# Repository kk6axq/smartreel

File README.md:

# SmartReel

SmartReel is a smart storage rack for reels of surface-mount electronic
components that works hand-in-hand with [InvenTree](https://inventree.org/),
an open-source inventory management system. The rack is built from one or more
**reel modules**, each a row of slots; every slot senses whether a reel is
present, has an addressable RGB LED to guide the operator, and can be widened by
pulling **dividers**. A touchscreen **HMI** mounted on the rack is the operator's
control panel — it talks to the rack hardware over RS485 and to InvenTree over
HTTPS. InvenTree stays the single source of truth for inventory; SmartReel
records *where* each reel physically lives and lights slots to guide pick and
put-away. The operator scans a reel, the rack lights up, and the inventory
updates itself.

## Project status & disclaimer

This project was developed with substantial AI assistance (using large language
models as a coding and documentation aid). The hardware, firmware, and plugin
have been built and run on real SmartReel hardware, and the core workflows have
been exercised on the bench and in use — but this is **not infallible software**.
It has not been through formal verification or a third-party audit, it almost
certainly contains bugs, and both the code and the docs may be incomplete or
occasionally wrong.

Treat it as a working reference design, not a turnkey product:

- Review the code yourself before relying on it, and read
  [`docs/known-bugs.md`](docs/known-bugs.md) for known limitations.
- **Security:** the HMI currently talks to InvenTree over HTTPS *without*
  certificate verification (`setInsecure()`), so the auth token is exposed to
  on-path attackers. Do not deploy on an untrusted network until certificate
  pinning is in place — see [`docs/known-bugs.md`](docs/known-bugs.md).
- It is provided as-is, with no warranty. You are responsible for validating it
  for your own use, especially anything safety- or inventory-critical.

Issues and pull requests that fix bugs or fill gaps are welcome.

## Repository layout

```
esp32-hmi/         ESP32-S3 touchscreen HMI firmware (C++ / PlatformIO / LVGL)
core-fw/           RP2040 core firmware that drives the reel modules (C++ / PlatformIO)
inventree-plugin/  InvenTree server-side plugin (Python)
pcbs/              KiCad hardware designs
  CorePCB/           Core PCB
  ReelPCB/           reel module PCB
debug-fw/          Bench/debug tooling (not shipped)
  mock-inventree/    FastAPI stand-in for the plugin, used during HMI development
  core-hwtest/       RP2040 hardware bring-up test
  esp32-rs485-pintest/ standalone ESP32 RS485 pin-toggle tool
  inject.py          bench event injector (drives the core test rig over USB)
  sd-assets/         mock QR codes for bench-testing the scan->resolve flow
docs/              Project documentation (start at docs/README.md)
labels/            Printable slot label PDFs (make_labels.py; PDFs git-ignored)
scripts/           Flashing, SD deployment, QR generation helpers
```

## Documentation

The full documentation set lives under [`docs/`](docs/README.md). Start with the
[documentation index](docs/README.md), then dive into the manual chapters:

- [Concept of Operations](docs/manual/01-concept-of-operations.md) — what SmartReel is and the end-to-end workflows.
- [Hardware Structure](docs/manual/02-hardware.md) — rack, Core PCB, reel modules, LEDs, sensors, wiring.
- [Software Structure](docs/manual/03-software-architecture.md) — components, subsystems, and system data flow.
- [API Reference](docs/manual/04-api-reference.md) — the HMI↔plugin HTTP API and the RS485 wire protocol.
- [InvenTree Integration](docs/manual/05-inventree-integration.md) — the plugin, install/config, and the sync model.
- [Operator User Manual](docs/manual/06-operator-manual.md) — task-oriented guide for shop-floor operators.

## Build & flash

**HMI firmware** (`esp32-hmi/`) and **Core firmware** (`core-fw/`) are
[PlatformIO](https://platformio.org/) projects. Build and flash:

```bash
# HMI (ESP32-S3) — requires manual boot mode (hold BOOT, tap RESET, release BOOT)
cd esp32-hmi && pio run
./scripts/flash-hmi.sh

# Core (RP2040) — UF2 dropped onto the BOOTSEL drive
cd core-fw && pio run
./scripts/flash-core.sh
```

The flash scripts locate the boards by USB VID, so the order they are plugged in
does not matter. See [`scripts/`](scripts/) for SD deployment (`deploy-sd.sh`)
and QR generation helpers.

**InvenTree plugin** (`inventree-plugin/`) is a Python plugin installed into an
InvenTree instance. See [`inventree-plugin/README.md`](inventree-plugin/README.md)
for installation, configuration, and the docker dev workflow.

**Mock server** — for HMI development without a live InvenTree, the FastAPI mock
at [`debug-fw/mock-inventree/`](debug-fw/mock-inventree/) serves the same HTTPS
contract as the plugin. See its [README](debug-fw/mock-inventree/README.md).

## Tests

Host-runnable tests (no hardware or InvenTree install needed) live under
[`tests/`](tests/README.md): the shared RS485 frame codec (`cd tests && make`)
and the plugin's pure service logic (`cd inventree-plugin && python3
test_services.py`). The full contract is exercised against a live InvenTree by
`inventree-plugin/test_live.py` and `test_multirack.py`.

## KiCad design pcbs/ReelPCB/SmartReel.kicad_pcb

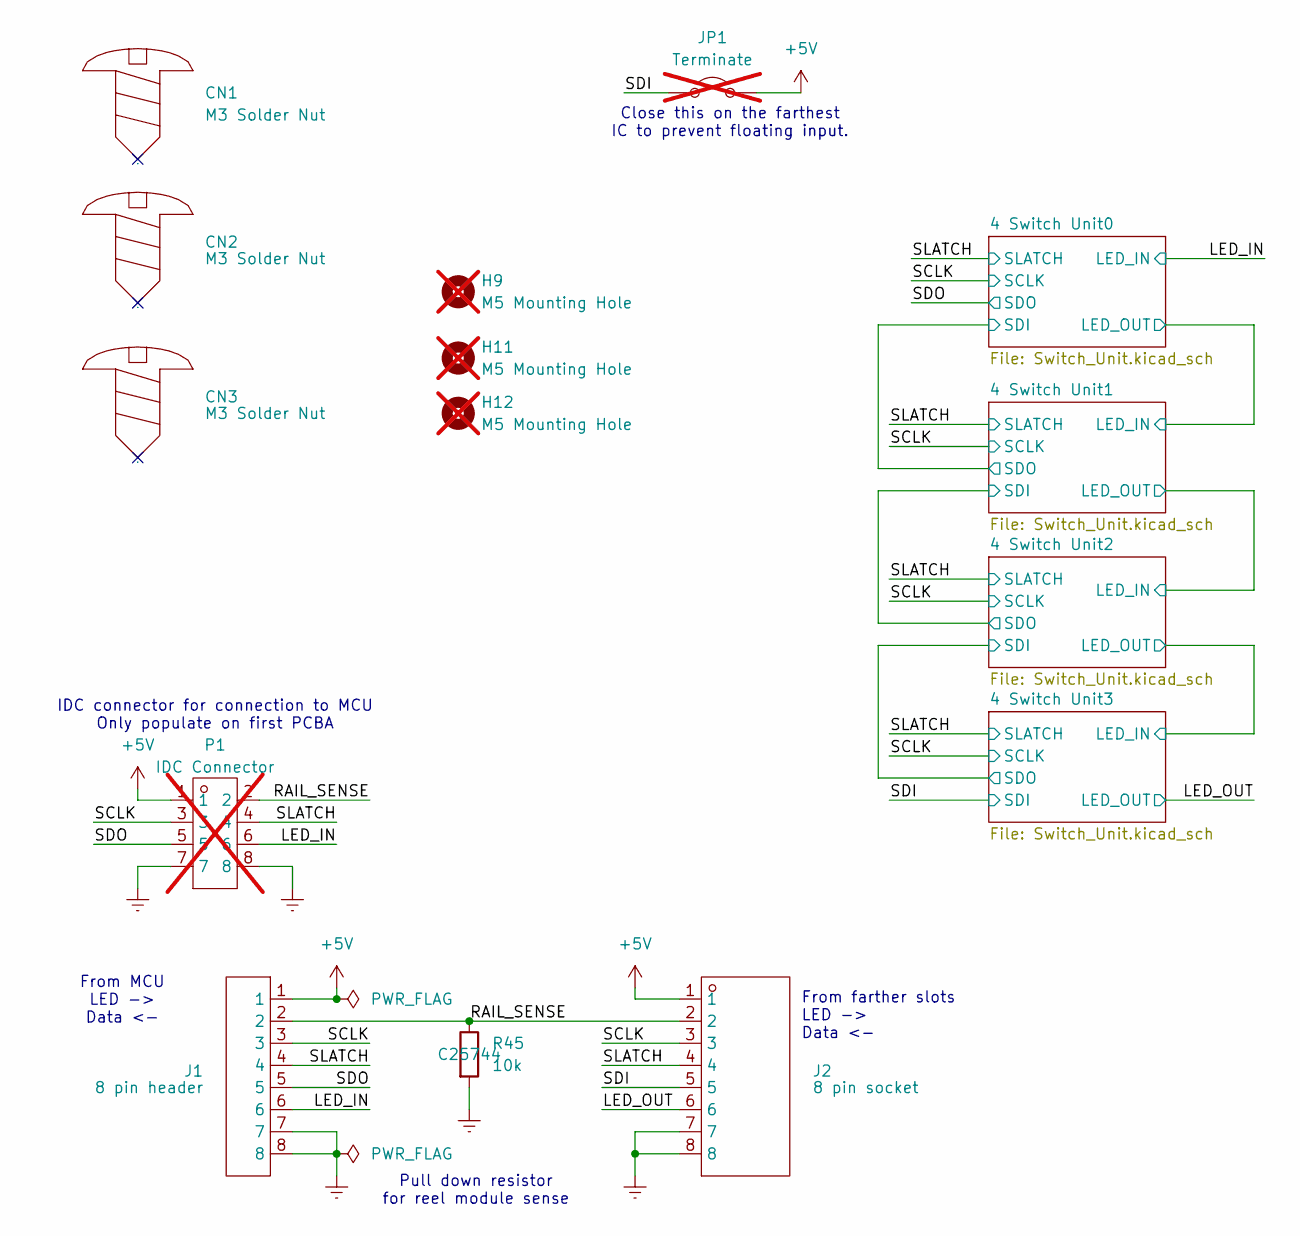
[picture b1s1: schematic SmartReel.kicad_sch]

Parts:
CN1, CN2, CN3: M3 Solder Nut; M3-TH_BD6.0-D4.3; Manufacturer Part SMTSOM330BTR; LCSC Part Name YIYUAN(怡远) 电路板表贴圆螺母柱 PCB贴片连接器 M3x5.56xL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
H9, H11, H12: M5 Mounting Hole; MountingHole_5.3mm_M5; not fitted
J1: 8 pin header; HDR-TH_8P-P2.54-H-M-W10.0; Manufacturer Part MTP125-1108R1; LCSC Part Name 1x8P 间距:2.54mm 方针 弯插
J2: 8 pin socket; HDR-TH_8P-P2.54-H-W8.6_A2541HWR-8P; Manufacturer Part A2541HWR-8P; LCSC Part Name 1x8P 间距:2.54mm 弯插
JP1: Terminate; SolderJumper-2_P1.3mm_Open_RoundedPad1.0x1.5mm; not fitted
P1: IDC Connector; IDC-TH_8P-P2.00_BOOMELE2X4P; Manufacturer Part 2.0-2*4P直简牛; LCSC Part Name 2mm 2x4P 排数:2 每排P数:4; not fitted
R45: 10k; R_0402_1005Metric

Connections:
+5V: J1.1, J2.1, JP1.2 (B), P1.1; also elsewhere on the board
/LED_IN: J1.6, P1.6; also elsewhere on the board
/LED_OUT: J2.6; also elsewhere on the board
/RAIL_SENSE: J1.2, J2.2, P1.2, R45.1
/SCLK: J1.3, J2.3, P1.3; also elsewhere on the board
/SDI: J2.5, JP1.1 (A); also elsewhere on the board
/SDO: J1.5, P1.5; also elsewhere on the board
/SLATCH: J1.4, J2.4, P1.4; also elsewhere on the board
Earth: J1.7, J1.8, J2.7, J2.8, P1.7, P1.8, R45.2; also elsewhere on the board

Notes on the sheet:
IDC connector for connection to MCU Only populate on first PCBA
Pull down resistor for reel module sense
Close this on the farthest IC to prevent floating input.
From MCU LED -> Data <-
From farther slots LED -> Data <-

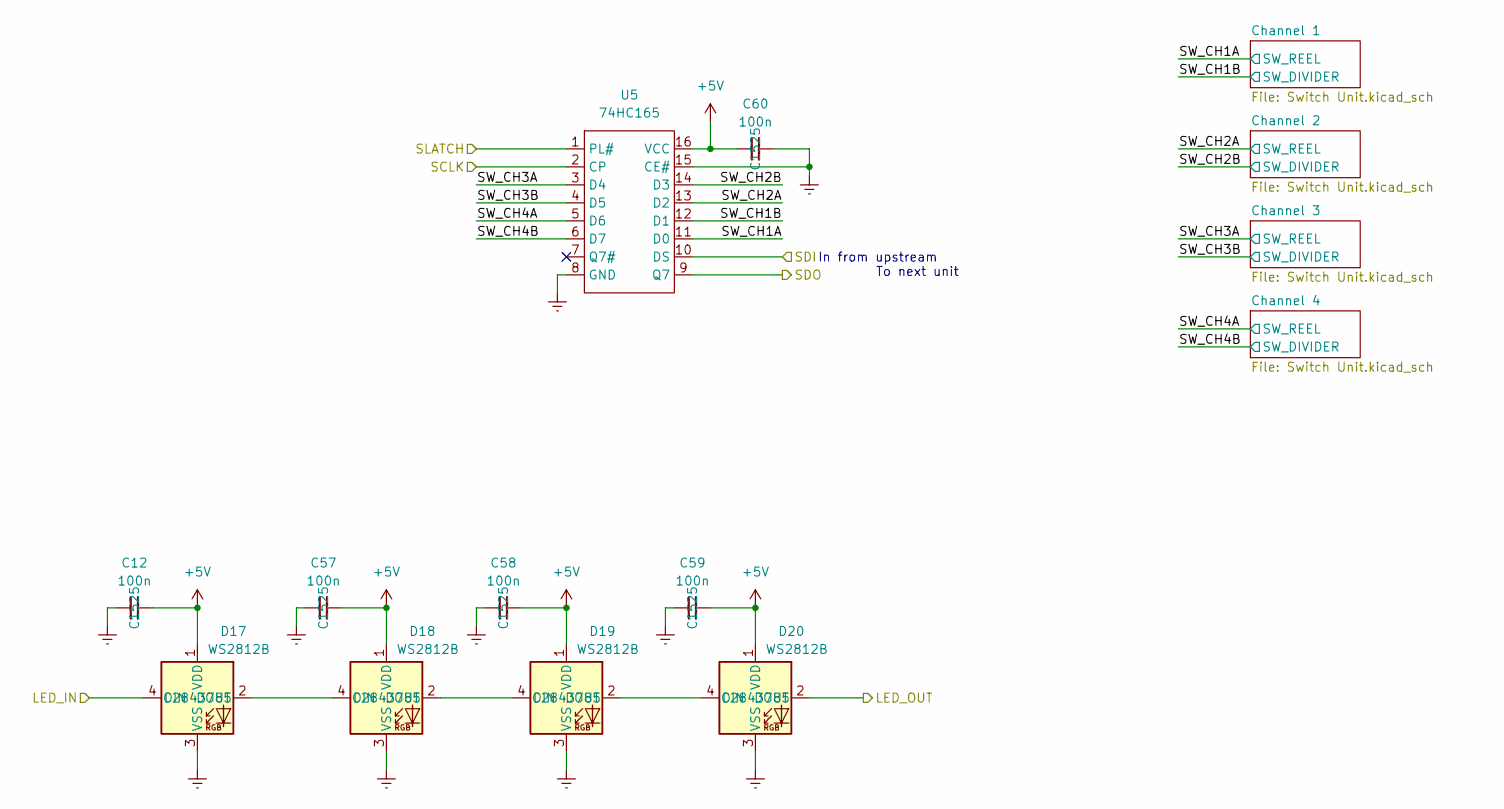
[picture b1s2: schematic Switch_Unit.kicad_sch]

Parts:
C12, C57, C58, C59, C60: 100n; C_0402_1005Metric
D17, D18, D19, D20: WS2812B; LED_WS2812B_PLCC4_5.0x5.0mm_P3.2mm
U5: 74HC165; SOIC-16_3.9x9.9mm_P1.27mm; Manufacturer Part 74HC165D,653; LCSC Part Name 补充型输出 并行或串行至串行移位寄存器

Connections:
+5V: C12.2, C57.2, C58.2, C59.2, C60.1, D17.1 (VDD), D18.1 (VDD), D19.1 (VDD), D20.1 (VDD), U5.16 (VCC); also elsewhere on the board
/4 Switch Unit0/LED_OUT: D20.2 (DOUT); also elsewhere on the board
/4 Switch Unit0/SDI: U5.10 (DS); also elsewhere on the board
/4 Switch Unit0/SW_CH1A: U5.11 (D0); also elsewhere on the board
/4 Switch Unit0/SW_CH1B: U5.12 (D1); also elsewhere on the board
/4 Switch Unit0/SW_CH2A: U5.13 (D2); also elsewhere on the board
/4 Switch Unit0/SW_CH2B: U5.14 (D3); also elsewhere on the board
/4 Switch Unit0/SW_CH3A: U5.3 (D4); also elsewhere on the board
/4 Switch Unit0/SW_CH3B: U5.4 (D5); also elsewhere on the board
/4 Switch Unit0/SW_CH4A: U5.5 (D6); also elsewhere on the board
/4 Switch Unit0/SW_CH4B: U5.6 (D7); also elsewhere on the board
/LED_IN: D17.4 (DIN); also elsewhere on the board
/SCLK: U5.2 (CP); also elsewhere on the board
/SDO: U5.9 (Q7); also elsewhere on the board
/SLATCH: U5.1 (PL#); also elsewhere on the board
Earth: C12.1, C57.1, C58.1, C59.1, C60.2, D17.3 (VSS), D18.3 (VSS), D19.3 (VSS), D20.3 (VSS), U5.8 (GND), U5.15 (CE#); also elsewhere on the board
unnamed: D17.2 (DOUT), D18.4 (DIN)
unnamed: D18.2 (DOUT), D19.4 (DIN)
unnamed: D19.2 (DOUT), D20.4 (DIN)

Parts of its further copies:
C11, C19, C20, C21, C22, C31, C32, C33, C34, C35, C44, C45, C46, C47, C48: 100n; C_0402_1005Metric
D5, D6, D7, D8, D9, D10, D11, D12, D13, D14, D15, D16: WS2812B; LED_WS2812B_PLCC4_5.0x5.0mm_P3.2mm
U2, U3, U4: 74HC165; SOIC-16_3.9x9.9mm_P1.27mm; Manufacturer Part 74HC165D,653; LCSC Part Name 补充型输出 并行或串行至串行移位寄存器

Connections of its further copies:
+5V: C11.2, C19.2, C20.2, C21.2, C22.1, C31.2, C32.2, C33.2, C34.2, C35.1, C44.2, C45.2, C46.2, C47.2, C48.1, D5.1 (VDD), D6.1 (VDD), D7.1 (VDD), D8.1 (VDD), D9.1 (VDD), D10.1 (VDD), D11.1 (VDD), D12.1 (VDD), D13.1 (VDD), D14.1 (VDD), D15.1 (VDD), D16.1 (VDD), U2.16 (VCC), U3.16 (VCC), U4.16 (VCC); also elsewhere on the board
/4 Switch Unit0/LED_OUT: D5.4 (DIN); also elsewhere on the board
/4 Switch Unit0/SDI: U2.9 (Q7); also elsewhere on the board
/4 Switch Unit1/LED_OUT: D8.2 (DOUT), D9.4 (DIN)
/4 Switch Unit1/SDI: U2.10 (DS), U3.9 (Q7)
/4 Switch Unit1/SW_CH1A: U2.11 (D0); also elsewhere on the board
/4 Switch Unit1/SW_CH1B: U2.12 (D1); also elsewhere on the board
/4 Switch Unit1/SW_CH2A: U2.13 (D2); also elsewhere on the board
/4 Switch Unit1/SW_CH2B: U2.14 (D3); also elsewhere on the board
/4 Switch Unit1/SW_CH3A: U2.3 (D4); also elsewhere on the board
/4 Switch Unit1/SW_CH3B: U2.4 (D5); also elsewhere on the board
/4 Switch Unit1/SW_CH4A: U2.5 (D6); also elsewhere on the board
/4 Switch Unit1/SW_CH4B: U2.6 (D7); also elsewhere on the board
/4 Switch Unit2/LED_OUT: D12.2 (DOUT), D13.4 (DIN)
/4 Switch Unit2/SDI: U3.10 (DS), U4.9 (Q7)
/4 Switch Unit2/SW_CH1A: U3.11 (D0); also elsewhere on the board
/4 Switch Unit2/SW_CH1B: U3.12 (D1); also elsewhere on the board
/4 Switch Unit2/SW_CH2A: U3.13 (D2); also elsewhere on the board
/4 Switch Unit2/SW_CH2B: U3.14 (D3); also elsewhere on the board
/4 Switch Unit2/SW_CH3A: U3.3 (D4); also elsewhere on the board
/4 Switch Unit2/SW_CH3B: U3.4 (D5); also elsewhere on the board
/4 Switch Unit2/SW_CH4A: U3.5 (D6); also elsewhere on the board
/4 Switch Unit2/SW_CH4B: U3.6 (D7); also elsewhere on the board
/4 Switch Unit3/SW_CH1A: U4.11 (D0); also elsewhere on the board
/4 Switch Unit3/SW_CH1B: U4.12 (D1); also elsewhere on the board
/4 Switch Unit3/SW_CH2A: U4.13 (D2); also elsewhere on the board
/4 Switch Unit3/SW_CH2B: U4.14 (D3); also elsewhere on the board
/4 Switch Unit3/SW_CH3A: U4.3 (D4); also elsewhere on the board
/4 Switch Unit3/SW_CH3B: U4.4 (D5); also elsewhere on the board
/4 Switch Unit3/SW_CH4A: U4.5 (D6); also elsewhere on the board
/4 Switch Unit3/SW_CH4B: U4.6 (D7); also elsewhere on the board
/LED_OUT: D16.2 (DOUT); also elsewhere on the board
/SCLK: U2.2 (CP), U3.2 (CP), U4.2 (CP); also elsewhere on the board
/SDI: U4.10 (DS); also elsewhere on the board
/SLATCH: U2.1 (PL#), U3.1 (PL#), U4.1 (PL#); also elsewhere on the board
Earth: C11.1, C19.1, C20.1, C21.1, C22.2, C31.1, C32.1, C33.1, C34.1, C35.2, C44.1, C45.1, C46.1, C47.1, C48.2, D5.3 (VSS), D6.3 (VSS), D7.3 (VSS), D8.3 (VSS), D9.3 (VSS), D10.3 (VSS), D11.3 (VSS), D12.3 (VSS), D13.3 (VSS), D14.3 (VSS), D15.3 (VSS), D16.3 (VSS), U2.8 (GND), U2.15 (CE#), U3.8 (GND), U3.15 (CE#), U4.8 (GND), U4.15 (CE#); also elsewhere on the board
unnamed: D5.2 (DOUT), D6.4 (DIN)
unnamed: D6.2 (DOUT), D7.4 (DIN)
unnamed: D7.2 (DOUT), D8.4 (DIN)
unnamed: D9.2 (DOUT), D10.4 (DIN)
unnamed: D10.2 (DOUT), D11.4 (DIN)
unnamed: D11.2 (DOUT), D12.4 (DIN)
unnamed: D13.2 (DOUT), D14.4 (DIN)
unnamed: D14.2 (DOUT), D15.4 (DIN)
unnamed: D15.2 (DOUT), D16.4 (DIN)

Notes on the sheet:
In from upstream
To next unit

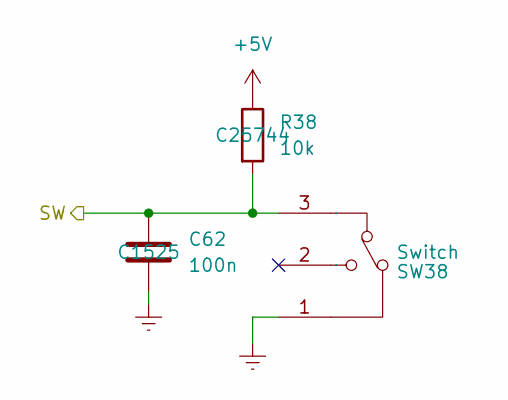
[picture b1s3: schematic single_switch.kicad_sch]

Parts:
C62: 100n; C_0402_1005Metric
R38: 10k; R_0402_1005Metric
SW38: Switch; SW-TH_SHOU-HAN_3JWD-DBHD-13.5; Manufacturer Part 3JWD-DBHD-13.5 125; LCSC Part Name 鼠标3脚微动 红点直柄13.5

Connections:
+5V: R38.1; also elsewhere on the board
/4 Switch Unit0/SW_CH4B: C62.1, R38.2, SW38.3 (NC); also elsewhere on the board
Earth: C62.2, SW38.1 (C); also elsewhere on the board

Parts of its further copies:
C23, C24, C25, C26, C27, C28, C29, C30, C36, C37, C38, C39, C40, C41, C42, C43, C49, C50, C51, C52, C53, C54, C55, C56, C61, C63, C64, C65, C66, C67, C68: 100n; C_0402_1005Metric
R13, R14, R15, R16, R17, R18, R19, R20, R21, R22, R23, R24, R25, R26, R27, R28, R29, R30, R31, R32, R33, R34, R35, R36, R37, R39, R40, R41, R42, R43, R44: 10k; R_0402_1005Metric
SW13, SW14, SW15, SW16, SW17, SW18, SW19, SW20, SW21, SW22, SW23, SW24, SW25, SW26, SW27, SW28, SW29, SW30, SW31, SW32, SW33, SW34, SW35, SW36, SW37, SW39, SW40, SW41, SW42, SW43, SW44: Switch; SW-TH_SHOU-HAN_3JWD-DBHD-13.5; Manufacturer Part 3JWD-DBHD-13.5 125; LCSC Part Name 鼠标3脚微动 红点直柄13.5

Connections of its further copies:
+5V: R13.1, R14.1, R15.1, R16.1, R17.1, R18.1, R19.1, R20.1, R21.1, R22.1, R23.1, R24.1, R25.1, R26.1, R27.1, R28.1, R29.1, R30.1, R31.1, R32.1, R33.1, R34.1, R35.1, R36.1, R37.1, R39.1, R40.1, R41.1, R42.1, R43.1, R44.1; also elsewhere on the board
/4 Switch Unit0/SW_CH1A: C63.1, R39.2, SW39.3 (NC); also elsewhere on the board
/4 Switch Unit0/SW_CH1B: C64.1, R40.2, SW40.3 (NC); also elsewhere on the board
/4 Switch Unit0/SW_CH2A: C65.1, R41.2, SW41.3 (NC); also elsewhere on the board
/4 Switch Unit0/SW_CH2B: C66.1, R42.2, SW42.3 (NC); also elsewhere on the board
/4 Switch Unit0/SW_CH3A: C67.1, R43.2, SW43.3 (NC); also elsewhere on the board
/4 Switch Unit0/SW_CH3B: C68.1, R44.2, SW44.3 (NC); also elsewhere on the board
/4 Switch Unit0/SW_CH4A: C61.1, R37.2, SW37.3 (NC); also elsewhere on the board
/4 Switch Unit1/SW_CH1A: C25.1, R15.2, SW15.3 (NC); also elsewhere on the board
/4 Switch Unit1/SW_CH1B: C26.1, R16.2, SW16.3 (NC); also elsewhere on the board
/4 Switch Unit1/SW_CH2A: C27.1, R17.2, SW17.3 (NC); also elsewhere on the board
/4 Switch Unit1/SW_CH2B: C28.1, R18.2, SW18.3 (NC); also elsewhere on the board
/4 Switch Unit1/SW_CH3A: C29.1, R19.2, SW19.3 (NC); also elsewhere on the board
/4 Switch Unit1/SW_CH3B: C30.1, R20.2, SW20.3 (NC); also elsewhere on the board
/4 Switch Unit1/SW_CH4A: C23.1, R13.2, SW13.3 (NC); also elsewhere on the board
/4 Switch Unit1/SW_CH4B: C24.1, R14.2, SW14.3 (NC); also elsewhere on the board
/4 Switch Unit2/SW_CH1A: C38.1, R23.2, SW23.3 (NC); also elsewhere on the board
/4 Switch Unit2/SW_CH1B: C39.1, R24.2, SW24.3 (NC); also elsewhere on the board
/4 Switch Unit2/SW_CH2A: C40.1, R25.2, SW25.3 (NC); also elsewhere on the board
/4 Switch Unit2/SW_CH2B: C41.1, R26.2, SW26.3 (NC); also elsewhere on the board
/4 Switch Unit2/SW_CH3A: C42.1, R27.2, SW27.3 (NC); also elsewhere on the board
/4 Switch Unit2/SW_CH3B: C43.1, R28.2, SW28.3 (NC); also elsewhere on the board
/4 Switch Unit2/SW_CH4A: C36.1, R21.2, SW21.3 (NC); also elsewhere on the board
/4 Switch Unit2/SW_CH4B: C37.1, R22.2, SW22.3 (NC); also elsewhere on the board
/4 Switch Unit3/SW_CH1A: C51.1, R31.2, SW31.3 (NC); also elsewhere on the board
/4 Switch Unit3/SW_CH1B: C52.1, R32.2, SW32.3 (NC); also elsewhere on the board
/4 Switch Unit3/SW_CH2A: C53.1, R33.2, SW33.3 (NC); also elsewhere on the board
/4 Switch Unit3/SW_CH2B: C54.1, R34.2, SW34.3 (NC); also elsewhere on the board
/4 Switch Unit3/SW_CH3A: C55.1, R35.2, SW35.3 (NC); also elsewhere on the board
/4 Switch Unit3/SW_CH3B: C56.1, R36.2, SW36.3 (NC); also elsewhere on the board
/4 Switch Unit3/SW_CH4A: C49.1, R29.2, SW29.3 (NC); also elsewhere on the board
/4 Switch Unit3/SW_CH4B: C50.1, R30.2, SW30.3 (NC); also elsewhere on the board
Earth: C23.2, C24.2, C25.2, C26.2, C27.2, C28.2, C29.2, C30.2, C36.2, C37.2, C38.2, C39.2, C40.2, C41.2, C42.2, C43.2, C49.2, C50.2, C51.2, C52.2, C53.2, C54.2, C55.2, C56.2, C61.2, C63.2, C64.2, C65.2, C66.2, C67.2, C68.2, SW13.1 (C), SW14.1 (C), SW15.1 (C), SW16.1 (C), SW17.1 (C), SW18.1 (C), SW19.1 (C), SW20.1 (C), SW21.1 (C), SW22.1 (C), SW23.1 (C), SW24.1 (C), SW25.1 (C), SW26.1 (C), SW27.1 (C), SW28.1 (C), SW29.1 (C), SW30.1 (C), SW31.1 (C), SW32.1 (C), SW33.1 (C), SW34.1 (C), SW35.1 (C), SW36.1 (C), SW37.1 (C), SW39.1 (C), SW40.1 (C), SW41.1 (C), SW42.1 (C), SW43.1 (C), SW44.1 (C); also elsewhere on the board

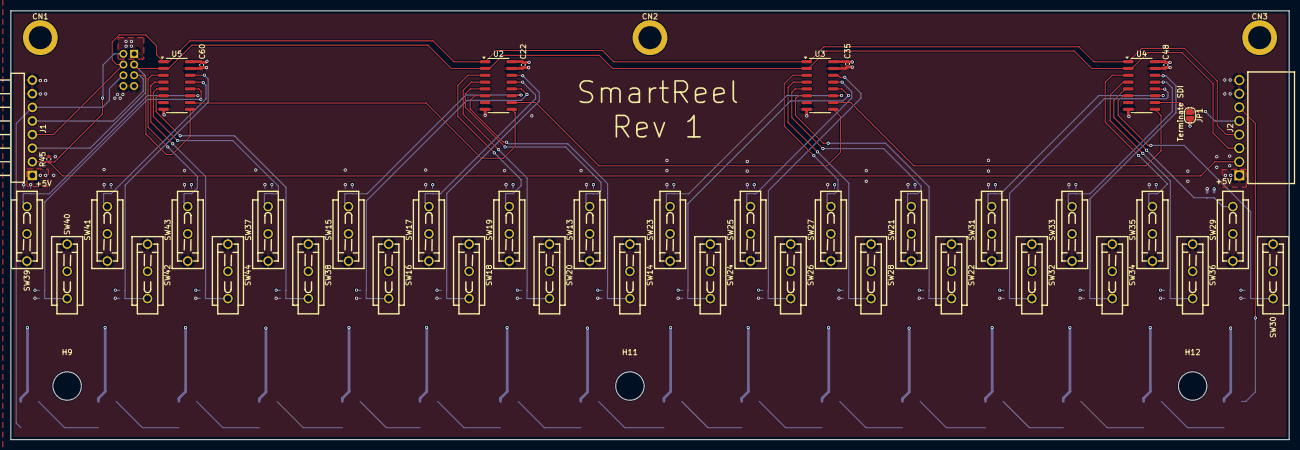
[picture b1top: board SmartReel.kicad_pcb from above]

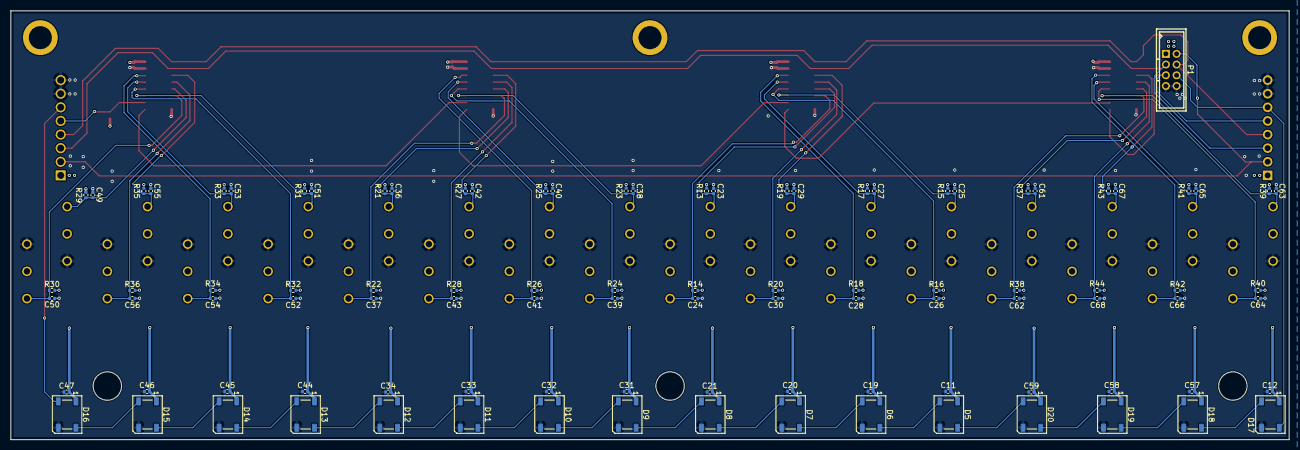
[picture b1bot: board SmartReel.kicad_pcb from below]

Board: 4 copper layers, 238.5 x 80.0 mm, 147 parts (97 on the bottom side), 59 nets.

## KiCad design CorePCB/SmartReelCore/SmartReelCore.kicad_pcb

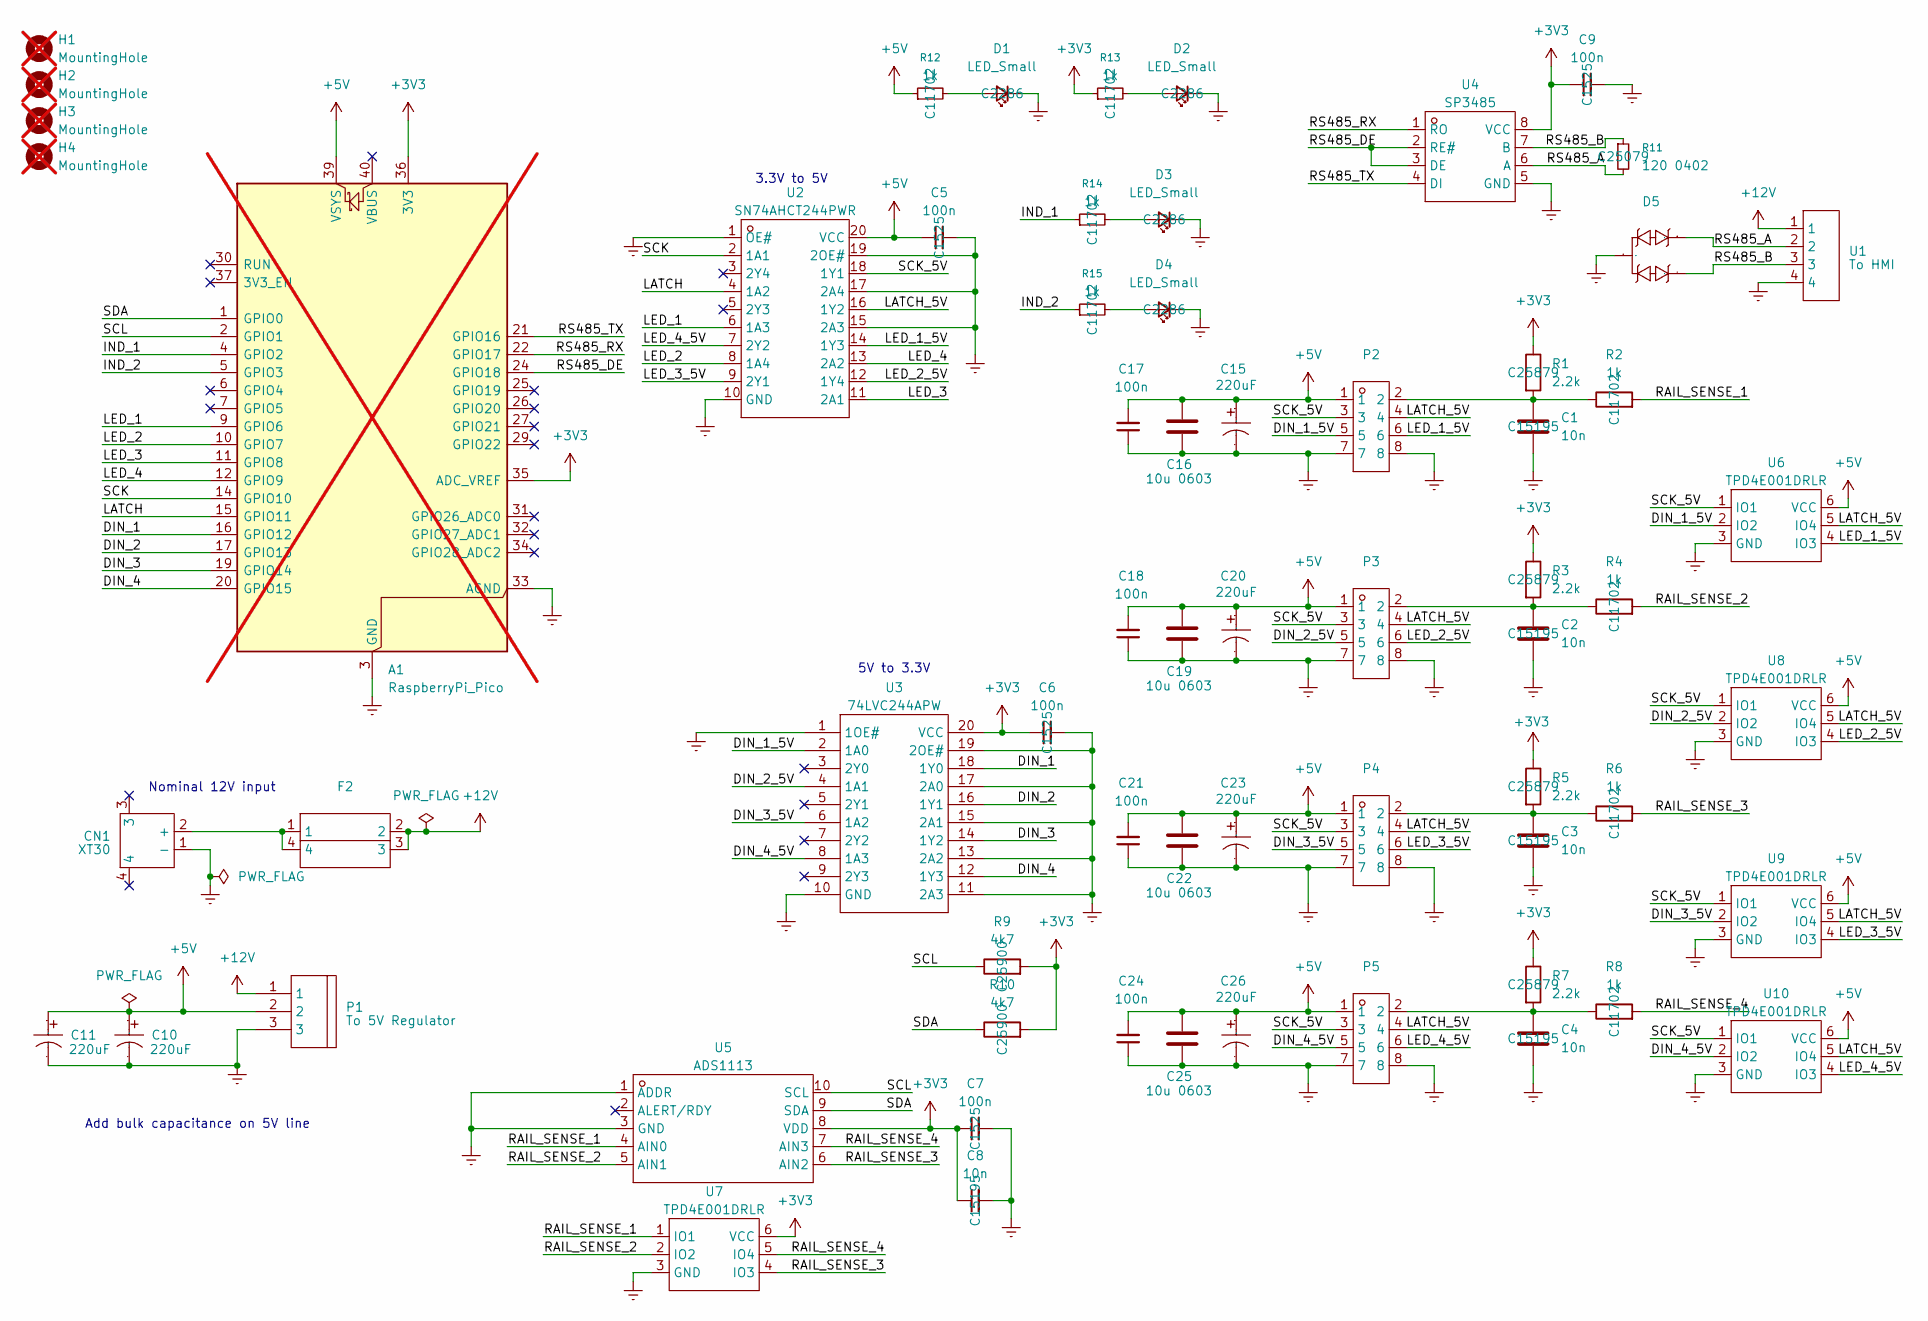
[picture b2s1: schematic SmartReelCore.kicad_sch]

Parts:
A1: RaspberryPi_Pico; RaspberryPi_Pico_Common_Unspecified; not fitted
C1, C2, C3, C4, C8: 10n; C_0402_1005Metric
C5, C6, C7, C9, C17, C18, C21, C24: 100n; C_0402_1005Metric
C10, C11, C15, C20, C23, C26: 220uF; CAP-SMD_BD8.0-L8.3-W8.3-LS9.3-FD; Manufacturer Part RVT1V221M0810; LCSC Part Name 220uF ±20% 35V
C16, C19, C22, C25: 10u 0603; C_0603_1608Metric
CN1: XT30; CONN-TH_XT30PW-M; Manufacturer Part XT30PW-M30.G.Y; LCSC Part Name AMASS(艾迈斯)航模插头电调机插座锂电池连接器 PCB板卧式 公头XT30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
D1, D2, D3, D4: LED_Small; LED_0603_1608Metric
D5: SOT-23-3_L2.9-W1.3-P1.90-LS2.4-BR; Manufacturer Part SM712-02HTG; LCSC Part Name SM712-02HTG
F2: FUSE-TH_4P-L16.0-W6.7; Manufacturer Part XF-508P-B-B; LCSC Part Name 汽车保险丝座 小号
H1, H2, H3, H4: MountingHole; MountingHole_3.2mm_M3_Pad; not fitted
P1: To 5V Regulator; CONN-TH_3P-P5.00_WJ500V-5.08-3P; Manufacturer Part WJ500V-5.08-03P-14-00A; LCSC Part Name 5.08mm 1x3P 排数:1 每排P数:3 直插
P2, P3, P4, P5: IDC-TH_8P-P2.00_BOOMELE2X4P; Manufacturer Part 2.0-2*4P直简牛; LCSC Part Name 2mm 2x4P 排数:2 每排P数:4
R1, R3, R5, R7: 2.2k; R_0402_1005Metric
R2, R4, R6, R8, R12, R13, R14, R15: 1k; R_0402_1005Metric
R9, R10: 4k7; R_0402_1005Metric
R11: 120 0402; R_0402_1005Metric
U1: To HMI; CONN-TH_WJ500V-5.08-4P; Manufacturer Part WJ500V-5.08-04P-14-00A; LCSC Part Name 5.08mm 直插 排数:1 每排P数:4
U2: SN74AHCT244PWR; TSSOP-20_L6.5-W4.4-P0.65-LS6.4-BL; Manufacturer Part SN74AHCT244PWR; LCSC Part Name SN74AHCT244PWR
U3: 74LVC244APW; TSSOP-20_L6.5-W4.4-P0.65-LS6.4-BL; Manufacturer Part 74LVC244APW,118; LCSC Part Name 三态输出，八路缓冲器/线路驱动器
U4: SP3485; SOIC-8_L5.0-W4.0-P1.27-LS6.0-BL; Manufacturer Part SP3485EN-L/TR; LCSC Part Name SP3485 +3.3V低功耗半双工RS-485收发器，数据速率10Mbps
U5: ADS1113; VSSOP-10_L3.0-W3.0-P0.50-LS4.9-BL; Manufacturer Part ADS1115IDGST; LCSC Part Name 具有内部基准、振荡器和可编程比较器且兼容 I2C 的ADS111x、超小型、低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
U6, U7, U8, U9, U10: TPD4E001DRLR; SOT-563_L1.6-W1.2-P0.50-LS1.6-BL; Manufacturer Part TPD4E001DRLR; LCSC Part Name 低电容TVS二极管

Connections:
+3V3: A1.35 (ADC_VREF), A1.36 (3V3), C6.1, C7.1, C8.1, C9.1, R1.1, R3.1, R5.1, R7.1, R9.2, R10.2, R13.1, U3.20 (VCC), U4.8 (VCC), U5.8 (VDD), U7.6 (VCC)
+5V: A1.39 (VSYS), C5.1, C10.1, C11.1, C15.1, C16.1, C17.2, C18.2, C19.1, C20.1, C21.2, C22.1, C23.1, C24.2, C25.1, C26.1, P1.2, P2.1, P3.1, P4.1, P5.1, R12.1, U2.20 (VCC), U6.6 (VCC), U8.6 (VCC), U9.6 (VCC), U10.6 (VCC)
+12V: F2.2, F2.3, P1.1, U1.1
/DIN_1: A1.16 (GPIO12), U3.18 (1Y0)
/DIN_1_5V: P2.5, U3.2 (1A0), U6.2 (IO2)
/DIN_2: A1.17 (GPIO13), U3.16 (1Y1)
/DIN_2_5V: P3.5, U3.4 (1A1), U8.2 (IO2)
/DIN_3: A1.19 (GPIO14), U3.14 (1Y2)
/DIN_3_5V: P4.5, U3.6 (1A2), U9.2 (IO2)
/DIN_4: A1.20 (GPIO15), U3.12 (1Y3)
/DIN_4_5V: P5.5, U3.8 (1A3), U10.2 (IO2)
/IND_1: A1.4 (GPIO2), R14.1
/IND_2: A1.5 (GPIO3), R15.1
/LATCH: A1.15 (GPIO11), U2.4 (1A2)
/LATCH_5V: P2.4, P3.4, P4.4, P5.4, U2.16 (1Y2), U6.5 (IO4), U8.5 (IO4), U9.5 (IO4), U10.5 (IO4)
/LED_1: A1.9 (GPIO6), U2.6 (1A3)
/LED_1_5V: P2.6, U2.14 (1Y3), U6.4 (IO3)
/LED_2: A1.10 (GPIO7), U2.8 (1A4)
/LED_2_5V: P3.6, U2.12 (1Y4), U8.4 (IO3)
/LED_3: A1.11 (GPIO8), U2.11 (2A1)
/LED_3_5V: P4.6, U2.9 (2Y1), U9.4 (IO3)
/LED_4: A1.12 (GPIO9), U2.13 (2A2)
/LED_4_5V: P5.6, U2.7 (2Y2), U10.4 (IO3)
/RAIL_SENSE_1: R2.2, U5.4 (AIN0), U7.1 (IO1)
/RAIL_SENSE_2: R4.2, U5.5 (AIN1), U7.2 (IO2)
/RAIL_SENSE_3: R6.2, U5.6 (AIN2), U7.4 (IO3)
/RAIL_SENSE_4: R8.2, U5.7 (AIN3), U7.5 (IO4)
/RS485_A: D5.1, R11.2, U1.2, U4.6 (A)
/RS485_B: D5.2, R11.1, U1.3, U4.7 (B)
/RS485_DE: A1.24 (GPIO18), U4.2 (RE#), U4.3 (DE)
/RS485_RX: A1.22 (GPIO17), U4.1 (RO)
/RS485_TX: A1.21 (GPIO16), U4.4 (DI)
/SCK: A1.14 (GPIO10), U2.2 (1A1)
/SCK_5V: P2.3, P3.3, P4.3, P5.3, U2.18 (1Y1), U6.1 (IO1), U8.1 (IO1), U9.1 (IO1), U10.1 (IO1)
/SCL: A1.2 (GPIO1), R9.1, U5.10 (SCL)
/SDA: A1.1 (GPIO0), R10.1, U5.9 (SDA)
Earth: A1.3 (GND), A1.8 (GND), A1.13 (GND), A1.18 (GND), A1.23 (GND), A1.28 (GND), A1.33 (AGND), A1.38 (GND), C1.2, C2.2, C3.2, C4.2, C5.2, C6.2, C7.2, C8.2, C9.2, C10.2, C11.2, C15.2, C16.2, C17.1, C18.1, C19.2, C20.2, C21.1, C22.2, C23.2, C24.1, C25.2, C26.2, CN1.1 (-), D1.1 (K), D2.1 (K), D3.1 (K), D4.1 (K), D5.3, P1.3, P2.7, P2.8, P3.7, P3.8, P4.7, P4.8, P5.7, P5.8, U1.4, U2.1 (OE#), U2.10 (GND), U2.15 (2A3), U2.17 (2A4), U2.19 (2OE#), U3.1 (1OE#), U3.10 (GND), U3.11 (2A3), U3.13 (2A2), U3.15 (2A1), U3.17 (2A0), U3.19 (2OE#), U4.5 (GND), U5.1 (ADDR), U5.3 (GND), U6.3 (GND), U7.3 (GND), U8.3 (GND), U9.3 (GND), U10.3 (GND)
unnamed: C1.1, P2.2, R1.2, R2.1
unnamed: C2.1, P3.2, R3.2, R4.1
unnamed: C3.1, P4.2, R5.2, R6.1
unnamed: C4.1, P5.2, R7.2, R8.1
unnamed: CN1.2 (+), F2.1, F2.4
unnamed: D1.2 (A), R12.2
unnamed: D2.2 (A), R13.2
unnamed: D3.2 (A), R14.2
unnamed: D4.2 (A), R15.2

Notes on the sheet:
Add bulk capacitance on 5V line
Nominal 12V input
3.3V to 5V
5V to 3.3V

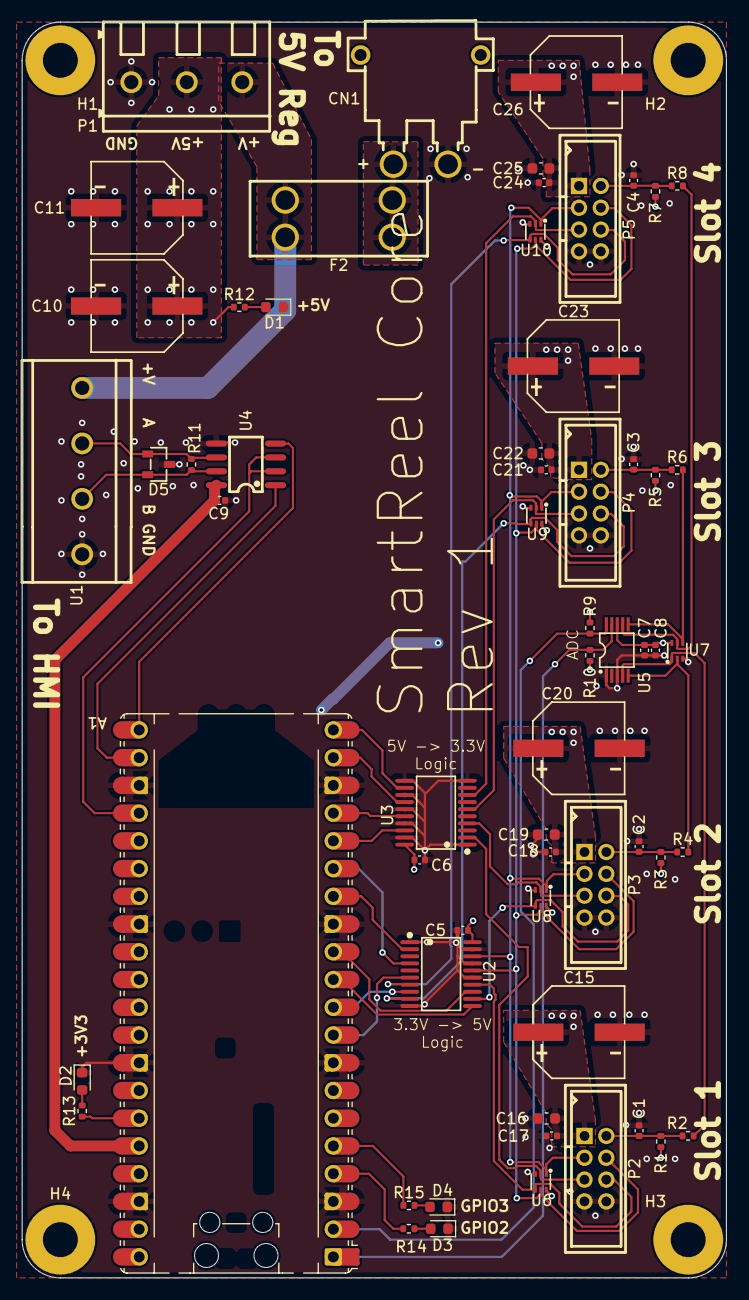
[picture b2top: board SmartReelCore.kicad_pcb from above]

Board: 4 copper layers, 64.5 x 115.0 mm, 65 parts (0 on the bottom side), 46 nets.

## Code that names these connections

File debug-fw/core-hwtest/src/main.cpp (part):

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//  Throwaway diagnostic that drives the slot hardware DIRECTLY (no RS485,
//  no protocol). Confirms three subsystems on the Core PCB:
//
//    1. WS2812B LEDs   -- one data line per slot: GPIO6/7/8/9 (slots 1-4)
//    2. ADS1115 ADC    -- I2C0 SDA=GPIO0 SCL=GPIO1, AIN0-3 = reel detect 1-4
//    3. 74HC165 PISO   -- shared SCK=GPIO10, LATCH=GPIO11;
//                         DIN per slot = GPIO12/13/14/15 (slots 1-4)
//
//  Reel-detect divider (per slot rail):
//    2.2k pull-up to 3.3V, and each inserted reel module adds a 10k
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    while (!Serial && (millis() - t0) < 2000) { /* wait */ }

    Serial.println(F("\n[boot] SmartReel Core HARDWARE TEST"));
    Serial.printf("[boot] LEDs GPIO%u/%u/%u/%u (%u px/slot)  SR SCK=%u LATCH=%u DIN=%u/%u/%u/%u (%u bits)\n",
                  LED_PIN[0], LED_PIN[1], LED_PIN[2], LED_PIN[3], LEDS_PER_SLOT,
                  SR_SCK, SR_LATCH, SR_DIN[0], SR_DIN[1], SR_DIN[2], SR_DIN[3], SR_BITS);
    Serial.printf("[boot] ADS1115 @0x%02X on I2C SDA=%u SCL=%u -- %s\n",
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
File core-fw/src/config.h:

// =====================================================================
//  SmartReel Core -- production firmware configuration
//
//  Pin map and hardware tunables for the Core PCB (RP2040). The pin
//  assignments here match the bring-up test (core-hwtest) verbatim --
//  that test confirmed all three slot subsystems on real hardware.
//
//  Hardware model
//  --------------
//  Four PORTS (0..3), each a physical connector on the Core PCB:
//      - one WS2812B data line          (GP6/7/8/9)
//      - one ADS1115 sense channel       (AIN0..3)
//      - one 74HC165 shift chain DIN     (GP12/13/14/15)
//        with SHARED clock (GP10) + latch (GP11)
//
//  Each port carries one or more chained reel MODULES. A module is a
//  pluggable strip of 16 reel-slots + 16 dividers:
//      - 16 WS2812B LEDs   (so a port's LED chain = 16 * n_modules)
//      - 32 input bits      (four 74HC165s; port chain = 32 * n_modules,
//        interleaved divider/slot: D0 S0 D1 S1 ... D15 S15)
//
//  The number of modules on a port is sensed from a voltage divider:
//  a 2.2k pull-up to 3.3V, plus a 10k pull-down per inserted module (so
//  n modules present 10k/n in parallel). See module_count_from_mv().
// =====================================================================
#pragma once

#include <stdint.h>

namespace cfg {

// ---- Port topology -------------------------------------------------
static constexpr uint8_t  N_PORTS            = 4;
static constexpr uint8_t  PORT_ALL           = 0xFF;   // "all ports" sentinel (matches rs485::REEL_ID_ALL)
static constexpr uint8_t  MODULE_LEDS        = 16;   // WS2812B per module
static constexpr uint8_t  MODULE_INPUT_BITS  = 32;   // 74HC165 bits per module
static constexpr uint8_t  MAX_MODULES_PER_PORT = 4;  // ADC divider resolution ceiling

static constexpr uint16_t MAX_PIXELS_PER_PORT = MODULE_LEDS * MAX_MODULES_PER_PORT;       // 64
static constexpr uint16_t MAX_BITS_PER_PORT   = MODULE_INPUT_BITS * MAX_MODULES_PER_PORT; // 128

// ---- WS2812B (one data line per port) ------------------------------
// NeoPXL8 needs all 8 pins within an 8-pin window; 6..9 qualifies.
// Unused outputs are -1. Index order = port 0..3.
static constexpr int8_t   LED_PINS[8]   = { 6, 7, 8, 9, -1, -1, -1, -1 };
static constexpr uint8_t  LED_BRIGHTNESS_DEFAULT = 64;   // 0-255, global

// ---- 74HC165 PISO (shared clock + latch, one DIN per port) ---------
static constexpr uint8_t  SR_DIN[N_PORTS] = { 12, 13, 14, 15 };
static constexpr uint8_t  SR_SCK   = 10;   // shared shift clock  (74HC165 CP)
static constexpr uint8_t  SR_LATCH = 11;   // shared parallel load (74HC165 PL#, active LOW)

// ---- ADS1115 reel-sense ADC ----------------------------------------
static constexpr uint8_t  I2C_SDA  = 0;    // I2C0 -> ADS1115
static constexpr uint8_t  I2C_SCL  = 1;
static constexpr uint8_t  ADS_ADDR = 0x48; // ADDR pin -> GND

// Sense divider component values. Rail = 3.3V * Rpd / (Rpd + RPULLUP),
// where Rpd = RMODULE / n_modules (pull-downs in parallel).
static constexpr float    SENSE_VREF_MV  = 3300.0f;
static constexpr float    SENSE_RPULLUP  = 2200.0f;   // ohms
static constexpr float    SENSE_RMODULE  = 10000.0f;  // ohms, per module

// ---- RS485 link ----------------------------------------------------
static constexpr uint8_t  PIN_RS485_TX = 16;   // -> SP3485 DI
static constexpr uint8_t  PIN_RS485_RX = 17;   // <- SP3485 RO
static constexpr uint8_t  PIN_RS485_DE = 18;   // -> SP3485 DE + RE#
// 115200 to match the HMI's auto-direction transceiver (can't turn
// around fast enough for higher rates). See esp32-hmi RS485 notes.
static constexpr uint32_t RS485_BAUD   = 115200;

// ---- Debug LEDs (discrete, on the Core PCB) ------------------------
static constexpr uint8_t  PIN_DBG_LINK = 2;    // RS485 link health
static constexpr uint8_t  PIN_DBG_AUX  = 3;    // spare / activity blip

// ---- Timing --------------------------------------------------------
// Button sampling: comfortably above the >5 Hz floor. 100 Hz gives
// ~10 ms input latency and leaves the bus + LEDs plenty of headroom.
static constexpr uint32_t INPUT_SAMPLE_HZ   = 100;
static constexpr uint32_t INPUT_SAMPLE_MS   = 1000 / INPUT_SAMPLE_HZ;
// A change must persist this many consecutive samples to count (debounce).
static constexpr uint8_t  INPUT_DEBOUNCE_SAMPLES = 2;

// Sense sampling is slow (ADS1115 conversions) and presence changes
// are slow too -- round-robin one channel per tick at ~10 Hz/channel.
static constexpr uint32_t SENSE_SAMPLE_MS   = 25;   // per-channel step; 4 ch -> 10 Hz each

// RS485 link is "up" if a valid master frame arrived within this window.
static constexpr uint32_t LINK_TIMEOUT_MS   = 1000;

// ---- Module count from sense voltage -------------------------------
// Expected rail voltage (mV) for n modules on a port. n==0 is the open
// rail (~Vref). Returned by reference for diagnostics.
inline uint16_t sense_mv_for_count(uint8_t n) {
    if (n == 0) return (uint16_t)(SENSE_VREF_MV + 0.5f);
    float rpd = SENSE_RMODULE / (float)n;
    return (uint16_t)(SENSE_VREF_MV * rpd / (rpd + SENSE_RPULLUP) + 0.5f);
}

// Quantize a measured rail voltage to a module count by nearest expected
// level. mv < 0 (ADC fault) yields 0.
inline uint8_t module_count_from_mv(int mv) {
    if (mv < 0) return 0;
    uint8_t best = 0;
    int     best_err = 32767;
    for (uint8_t n = 0; n <= MAX_MODULES_PER_PORT; ++n) {
        int err = (int)mv - (int)sense_mv_for_count(n);
        if (err < 0) err = -err;
        if (err < best_err) { best_err = err; best = n; }
    }
    return best;
}

} // namespace cfg

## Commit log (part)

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2026-04-18 Initial version with photointerrupter
2026-05-11 Commit to upload
2026-05-11 Move files and route reel PCB
2026-05-11 Initial commit for core PCB
2026-05-18 Rev 1 PCBs ordered
